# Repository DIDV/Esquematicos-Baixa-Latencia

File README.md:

#Esquematicos Baixa Latência

Repositório dos esquematicos de baixa latência.

Commits baseados nas diferenças nos xmls gerados pelo software [Eagle](http://www.cadsoftusa.com/).

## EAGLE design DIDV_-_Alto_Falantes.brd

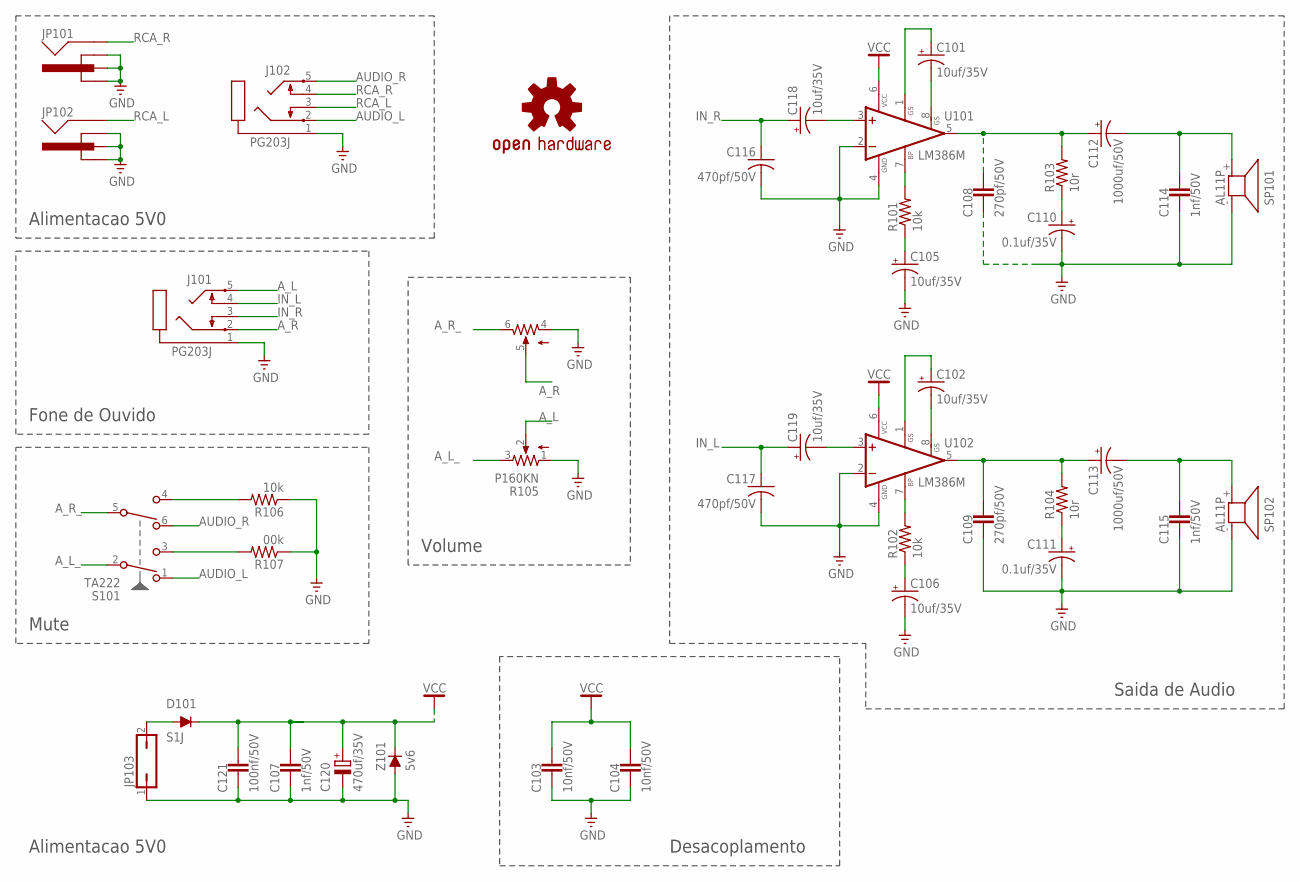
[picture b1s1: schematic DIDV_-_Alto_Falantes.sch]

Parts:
C101, C102, C105, C106, C118, C119: 10uf/35V; E2-5
C103, C104: 10nf/50V; C0805
C107, C114, C115: 1nf/50V; C0805
C108, C109: 270pf/50V; C0805
C110, C111: 0.1uf/35V; E2-5
C112, C113: 1000uf/50V; E3,5-10
C116, C117: 470pf/50V; C0603
C120: 470uf/35V; E3,5-10
C121: 100nf/50V; C0805
D101: S1J; DO214AC
J101, J102: PG203J
JP101, JP102: RCA
JP103: JP1Q; JP1
LOGO101: OSHW-LOGOL; OSHW-LOGO-L
R101, R102, R106: 10k; R1206
R103, R104: 10r; R1206
R105: P160KN
R107: 00k; R1206
S101: TA222
SP101, SP102: AL11P
U101, U102: LM386M; SO08
Z101: 5v6; SOT23

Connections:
AUDIO_L: J102.2, S101.1 (A-NC)
AUDIO_R: J102.5, S101.6 (B-NC)
A_L: J101.5, R105.2
A_L_: R105.3, S101.2 (A-COM)
A_R: J101.2, R105.5 (6)
A_R_: R105.6 (5), S101.5 (B-COM)
GND: C103.2, C104.2, C105.-, C106.-, C107.2, C108.2, C109.2, C110.-, C111.-, C114.2, C115.2, C116.2, C117.2, C120.-, C121.2, J101.1, J102.1, JP101._1GND (GND1), JP101._2GND (GND2), JP101._GND (GND), JP102._1GND (GND1), JP102._2GND (GND2), JP102._GND (GND), JP103.1, R105.1, R105.4, R106.1, R107.1, SP101.- (1), SP102.- (1), U101.2 (-IN), U101.4 (GND), U102.2 (-IN), U102.4 (GND), Z101.1 (A)
IN_L: C117.1, C119.+, J101.4
IN_R: C116.1, C118.+, J101.3
unnamed: C105.+, R101.1
unnamed: R101.2, U101.7 (BS2)
unnamed: C110.+, R103.1
unnamed: C108.1, C112.+, R103.2, U101.5 (OUT)
unnamed: C101.-, U101.8 (GAIN)
unnamed: C101.+, U101.1 (GAIN)
unnamed: C118.-, U101.3 (+IN)
unnamed: C113.-, C115.1, SP102.+ (2)
unnamed: C112.-, C114.1, SP101.+ (2)
unnamed: R106.2, S101.4 (B-NO)
unnamed: C106.+, R102.1
unnamed: R102.2, U102.7 (BS2)
unnamed: C111.+, R104.1
unnamed: C109.1, C113.+, R104.2, U102.5 (OUT)
unnamed: C102.-, U102.8 (GAIN)
unnamed: C102.+, U102.1 (GAIN)
unnamed: C119.-, U102.3 (+IN)
unnamed: R107.2, S101.3 (A-NO)
unnamed: D101.A, JP103.2
RCA_L: J102.3, JP102._SIGNAL (SIGNAL)
RCA_R: J102.4, JP101._SIGNAL (SIGNAL)
VCC: C103.1, C104.1, C107.1, C120.+, C121.1, D101.C, U101.6 (VS), U102.6 (VS), Z101.3 (C)

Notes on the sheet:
Alimentacao 5V0
Desacoplamento
Fone de Ouvido
Mute
Volume
Saida de Audio

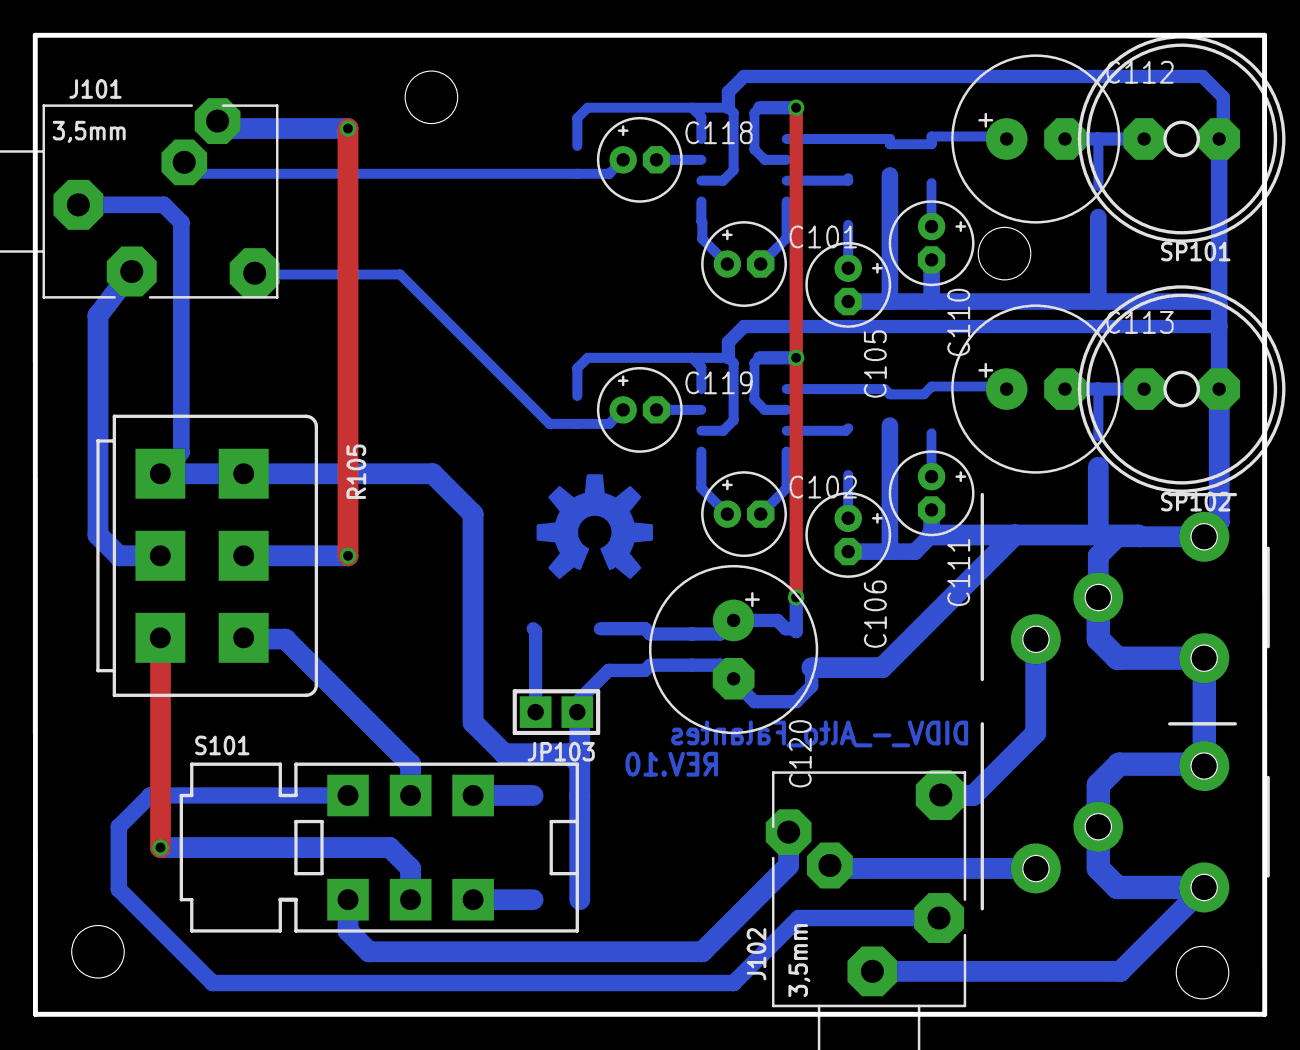
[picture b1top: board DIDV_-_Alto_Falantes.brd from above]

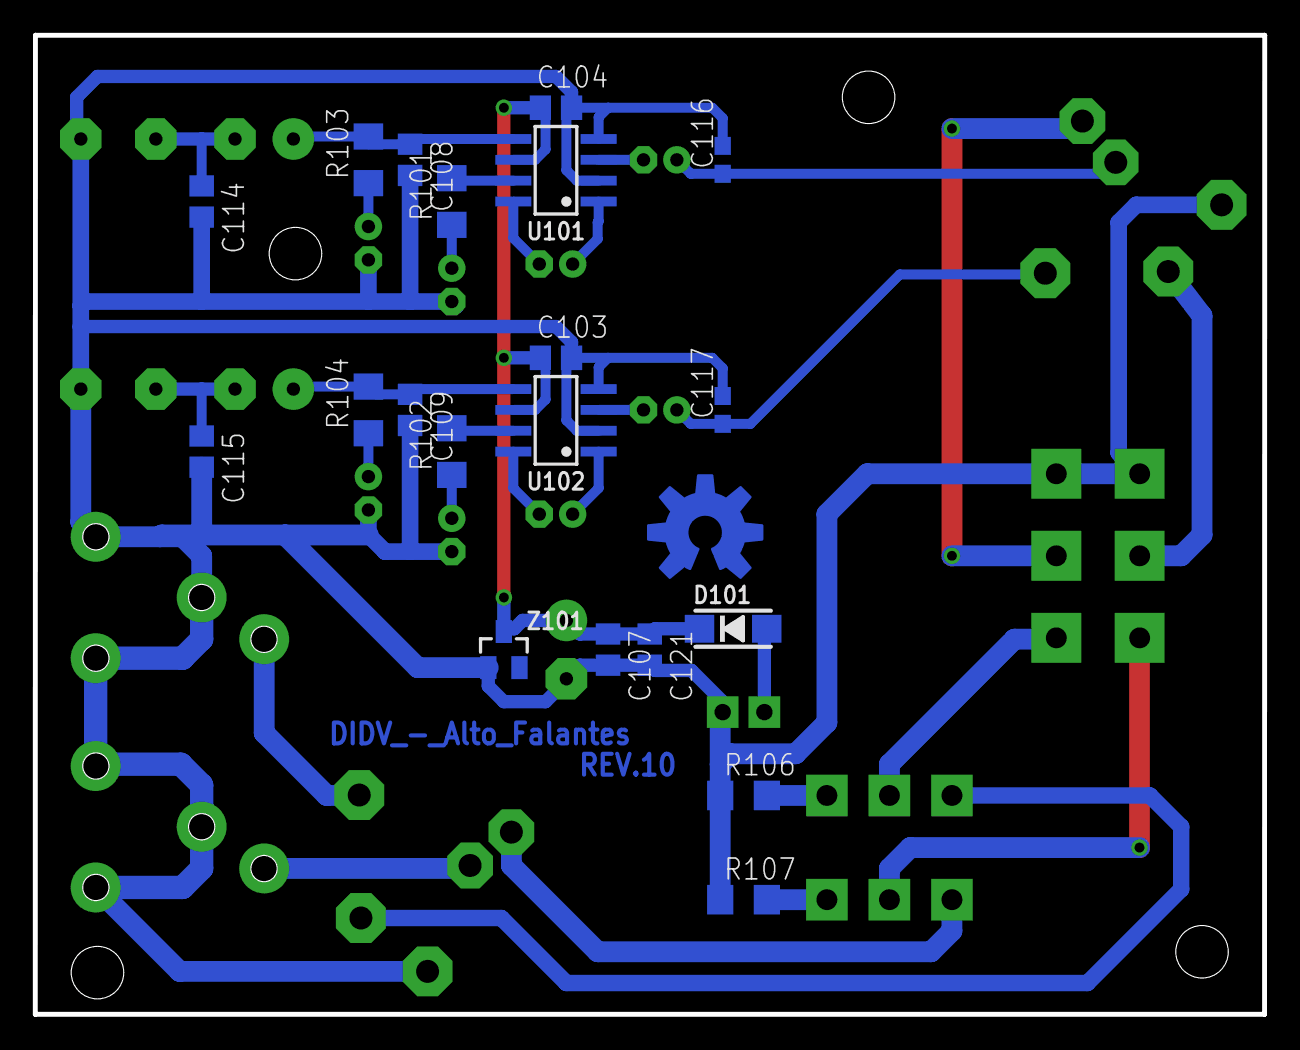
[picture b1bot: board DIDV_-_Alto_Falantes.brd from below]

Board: 2 copper layers, 74.9 x 59.7 mm, 41 parts (20 on the bottom side), 31 nets.

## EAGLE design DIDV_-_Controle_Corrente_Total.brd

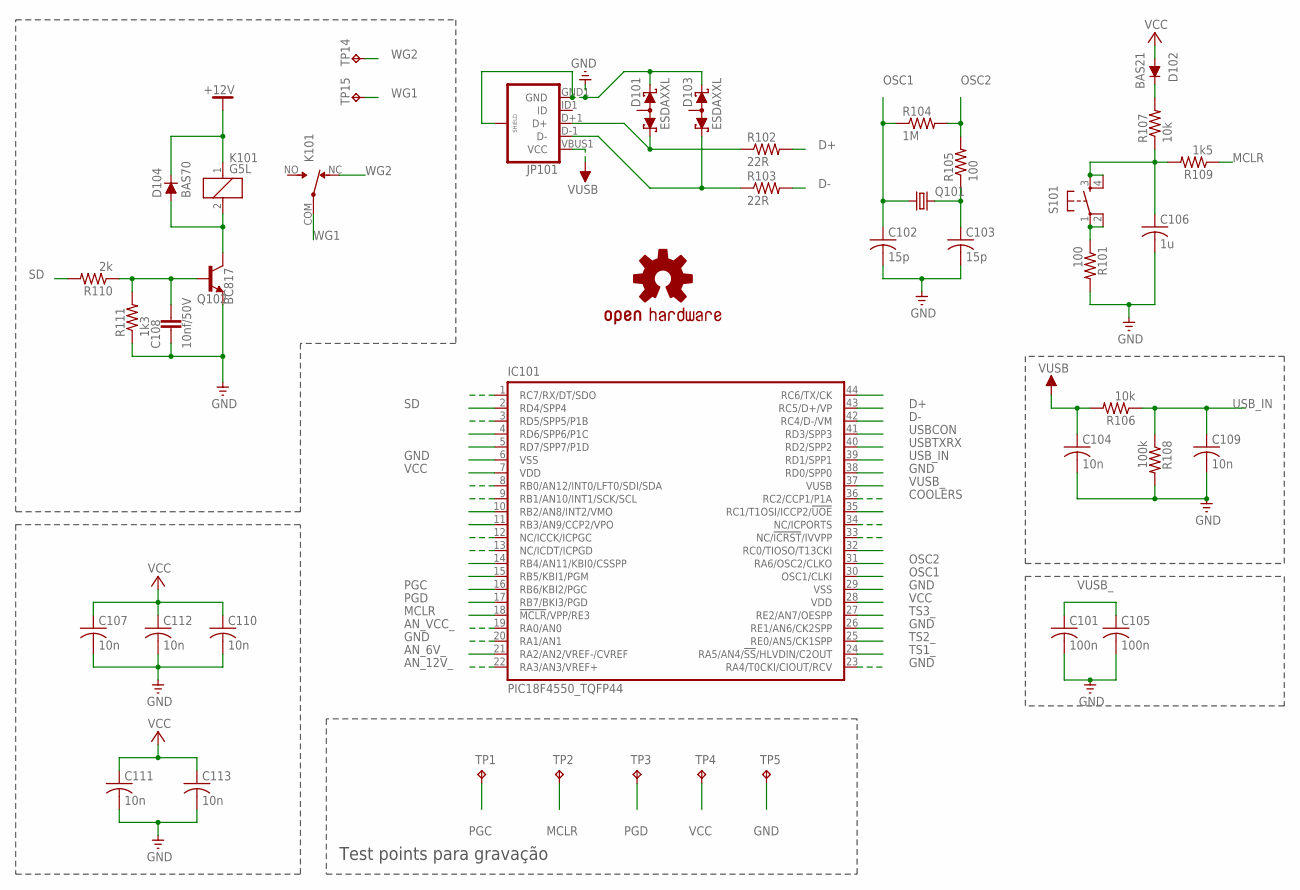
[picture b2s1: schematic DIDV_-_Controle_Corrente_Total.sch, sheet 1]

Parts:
C101, C105: 100n; C0603
C102, C103: 15p; C0603K
C104, C110, C111, C113: 10n; C0805K
C106: 1u; C0805K
C107, C112: 10n; C0603
C108: 10nf/50V; C0603K
C109: 10n; C0603K
D101, D103: ESDAXXL; SOT23
D102: BAS21; SOT23
D104: BAS70; SOT23
IC101: PIC18F4550_TQFP44; TQFP44
JP101: USB_MICROB_PLUGCONN-11752; USB-B-MICRO-SMD_V03
K101: G5L; G5LE
LOGO101: OSHW-LOGOL; OSHW-LOGO-L
Q101: CRYSTALSM49; SM49
Q102: BC817; SOT23-BEC
R101, R105: 100; R0603
R102, R103: 22R; R0603
R104: 1M; R0603
R106, R107: 10k; R0603
R108: 100k; R0603
R109: 1k5; R0603
R110: 2k; R0603
R111: 1k3; R0603
S101: TAC_SWITCHPTH; TACTILE-PTH
TP1, TP2, TP3, TP4, TP5: TPB1,27; B1,27
TP14, TP15: TP-063

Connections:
+12V: D104.3 (C), K101.1; also elsewhere on the board
AN_6V_: IC101.21 (RA2/AN2/VREF-/CVREF); also elsewhere on the board
AN_12V_: IC101.22 (RA3/AN3/VREF+); also elsewhere on the board
AN_VCC_: IC101.19 (RA0/AN0); also elsewhere on the board
COOLERS: IC101.36 (RC2/CCP1/P1A); also elsewhere on the board
D+: IC101.43 (RC5/D+/VP), R102.2
D-: IC101.42 (RC4/D-/VM), R103.2
GND: C101.2, C102.2, C103.2, C104.2, C105.2, C106.2, C107.2, C108.2, C109.2, C110.2, C111.2, C112.2, C113.2, D101.2 (C2), D103.2 (C2), IC101.6 (VSS), IC101.20 (RA1/AN1), IC101.23 (RA4/T0CKI/CIOUT/RCV), IC101.26 (RE1/AN6/CK2SPP), IC101.29 (VSS), IC101.38 (RD0/SPP0), JP101.GND1 (GND), JP101.SHIELD1 (SHIELD), JP101.SHIELD2 (SHIELD), JP101.SHIELD3 (SHIELD), Q102.E, R101.2, R108.2, R111.1, TP5.TP; also elsewhere on the board
MCLR: IC101.18 (!MCLR!/VPP/RE3), R109.1, TP2.TP
unnamed: C103.1, Q101.2, R105.1
unnamed: D102.3 (C), R107.2
unnamed: D104.1 (A), K101.2, Q102.C
unnamed: C108.1, Q102.B, R110.1, R111.2
unnamed: D103.1 (C1), JP101.D-1 (D-), R103.1
unnamed: D101.1 (C1), JP101.D+1 (D+), R102.1
unnamed: R101.1, S101.1, S101.2
OSC1: C102.1, IC101.30 (OSC1/CLKI), Q101.1, R104.1
OSC2: IC101.31 (RA6/OSC2/CLKO), R104.2, R105.2
PGC: IC101.16 (RB6/KBI2/PGC), TP1.TP
PGD: IC101.17 (RB7/BKI3/PGD), TP3.TP
SD: IC101.2 (RD4/SPP4), R110.2
TS1_: IC101.24 (RA5/AN4/!SS!/HLVDIN/C2OUT); also elsewhere on the board
TS2_: IC101.25 (RE0/AN5/CK1SPP); also elsewhere on the board
TS3_: IC101.27 (RE2/AN7/OESPP); also elsewhere on the board
USBCON: IC101.41 (RD3/SPP3); also elsewhere on the board
USBTXRX: IC101.40 (RD2/SPP2); also elsewhere on the board
USB_IN: C109.1, IC101.39 (RD1/SPP1), R106.1, R108.1
U_MCLR: C106.1, R107.1, R109.2, S101.3, S101.4
VCC: C107.1, C110.1, C111.1, C112.1, C113.1, D102.1 (A), IC101.7 (VDD), IC101.28 (VDD), TP4.TP; also elsewhere on the board
VUSB: C104.1, JP101.VBUS1 (VCC), R106.2
VUSB_: C101.1, C105.1, IC101.37 (VUSB)
WG1: K101.COM, TP15.1
WG2: K101.NC, TP14.1

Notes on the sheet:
Test points para gravação

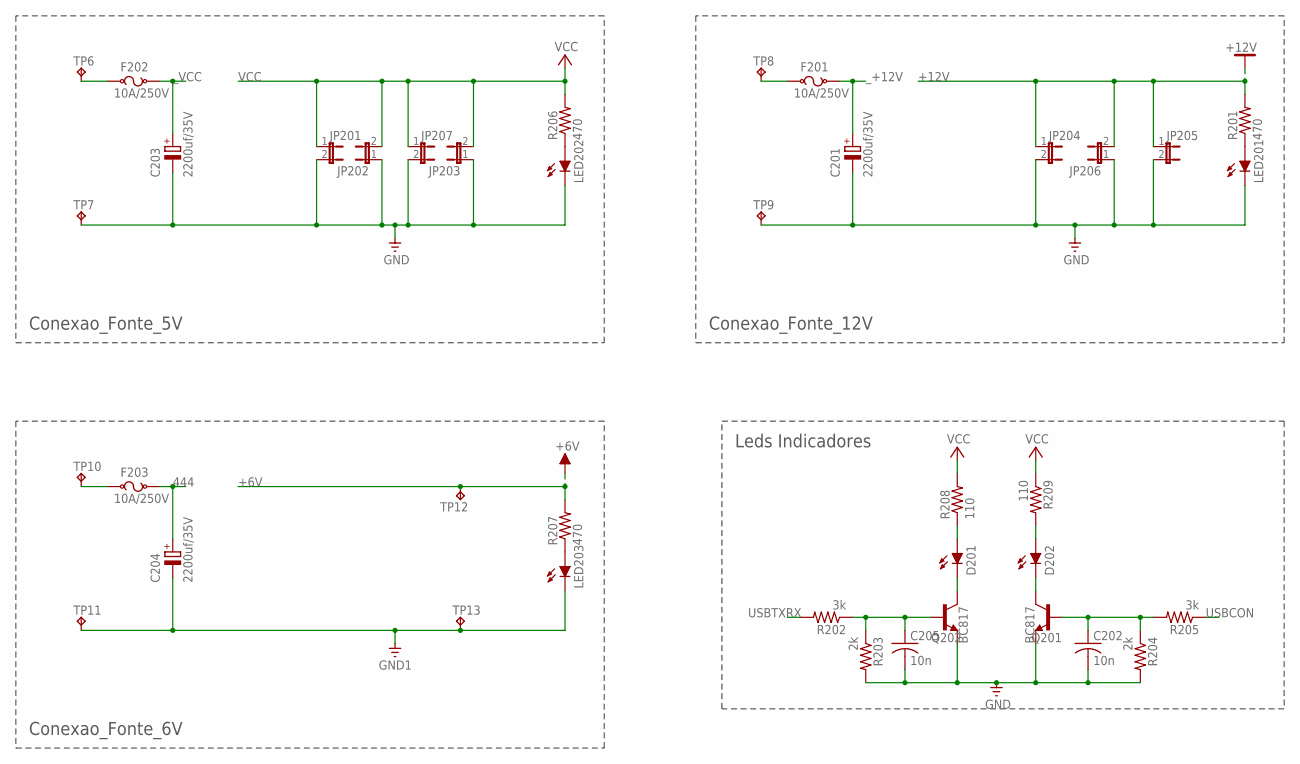
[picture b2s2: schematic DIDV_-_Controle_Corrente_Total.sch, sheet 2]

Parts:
C201, C203, C204: 2200uf/35V; E3,5-10
C202, C205: 10n; C0603
D201, D202: LEDTOPLED-SANTANA; MINI-TOPLED-SANTANA
F201, F202, F203: 10A/250V; KS9V
JP201, JP202, JP203, JP204, JP205, JP206, JP207: JP1EY; JP1Y
LED201, LED202, LED203: LEDP-LCC-2; P-LCC-2
Q201, Q202: BC817; SOT23-BEC
R201, R206, R207: 470; R1206
R202, R205: 3k; R0603
R203, R204: 2k; R0603
R208, R209: 110; R1206
TP6, TP7, TP8, TP9, TP10, TP11, TP12, TP13: TP-063

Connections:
444: C204.+, F203.2; also elsewhere on the board
+6V: R207.2, TP12.1; also elsewhere on the board
+12V: JP204.1, JP205.1, JP206.2, R201.2; also elsewhere on the board
GND: C201.-, C202.2, C203.-, C205.2, JP201.2, JP202.1, JP203.1, JP204.2, JP205.2, JP206.1, JP207.2, LED201.C, LED202.C, Q201.E, Q202.E, R203.2, R204.2, TP7.1, TP9.1; also elsewhere on the board
GND1: C204.-, LED203.C, TP11.1, TP13.1
unnamed: LED202.A, R206.1
unnamed: LED201.A, R201.1
unnamed: F201.1, TP8.1
unnamed: LED203.A, R207.1
unnamed: F203.1, TP10.1
unnamed: D201.A, R208.1
unnamed: D202.A, R209.2
unnamed: C205.1, Q202.B, R202.1, R203.1
unnamed: C202.1, Q201.B, R204.1, R205.2
unnamed: D201.C, Q202.C
unnamed: D202.C, Q201.C
unnamed: F202.1, TP6.1
USBCON: R205.1; also elsewhere on the board
USBTXRX: R202.2; also elsewhere on the board
VCC: JP201.1, JP202.2, JP203.2, JP207.1, R206.2, R208.2, R209.1; also elsewhere on the board
_+12V: C201.+, F201.2; also elsewhere on the board
_VCC: C203.+, F202.2; also elsewhere on the board

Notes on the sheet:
Conexao_Fonte_5V
Conexao_Fonte_12V
Conexao_Fonte_6V
Leds Indicadores

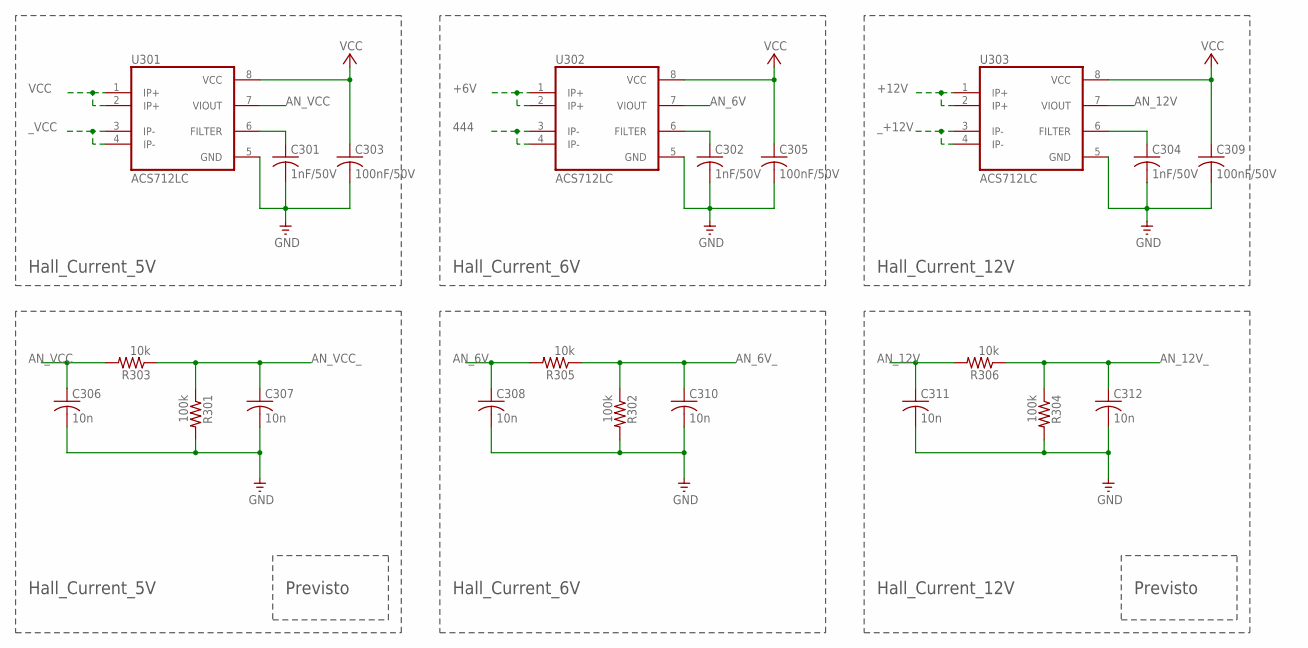
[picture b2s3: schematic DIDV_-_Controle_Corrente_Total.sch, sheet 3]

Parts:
C301, C302, C304: 1nF/50V; C0603
C303, C305, C309: 100nF/50V; C0805
C306, C308, C311: 10n; C0805K
C307, C310, C312: 10n; C0603K
R301, R302, R304: 100k; R0603
R303, R305, R306: 10k; R0603
U301, U302, U303: ACS712LC; SO08

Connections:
444: U302.3 (IP-), U302.4 (IP-); also elsewhere on the board
+6V: U302.1 (IP+), U302.2 (IP+); also elsewhere on the board
+12V: U303.1 (IP+), U303.2 (IP+); also elsewhere on the board
AN_6V: C308.1, R305.2, U302.7 (VIOUT)
AN_6V_: C310.1, R302.1, R305.1; also elsewhere on the board
AN_12V: C311.1, R306.2, U303.7 (VIOUT)
AN_12V_: C312.1, R304.1, R306.1; also elsewhere on the board
AN_VCC: C306.1, R303.2, U301.7 (VIOUT)
AN_VCC_: C307.1, R301.1, R303.1; also elsewhere on the board
GND: C301.2, C302.2, C303.2, C304.2, C305.2, C306.2, C307.2, C308.2, C309.2, C310.2, C311.2, C312.2, R301.2, R302.2, R304.2, U301.5 (GND), U302.5 (GND), U303.5 (GND); also elsewhere on the board
unnamed: C302.1, U302.6 (FILTER)
unnamed: C304.1, U303.6 (FILTER)
unnamed: C301.1, U301.6 (FILTER)
VCC: C303.1, C305.1, C309.1, U301.1 (IP+), U301.2 (IP+), U301.8 (VCC), U302.8 (VCC), U303.8 (VCC); also elsewhere on the board
_+12V: U303.3 (IP-), U303.4 (IP-); also elsewhere on the board
_VCC: U301.3 (IP-), U301.4 (IP-); also elsewhere on the board

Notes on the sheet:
Hall_Current_5V
Hall_Current_6V
Hall_Current_12V
Previsto

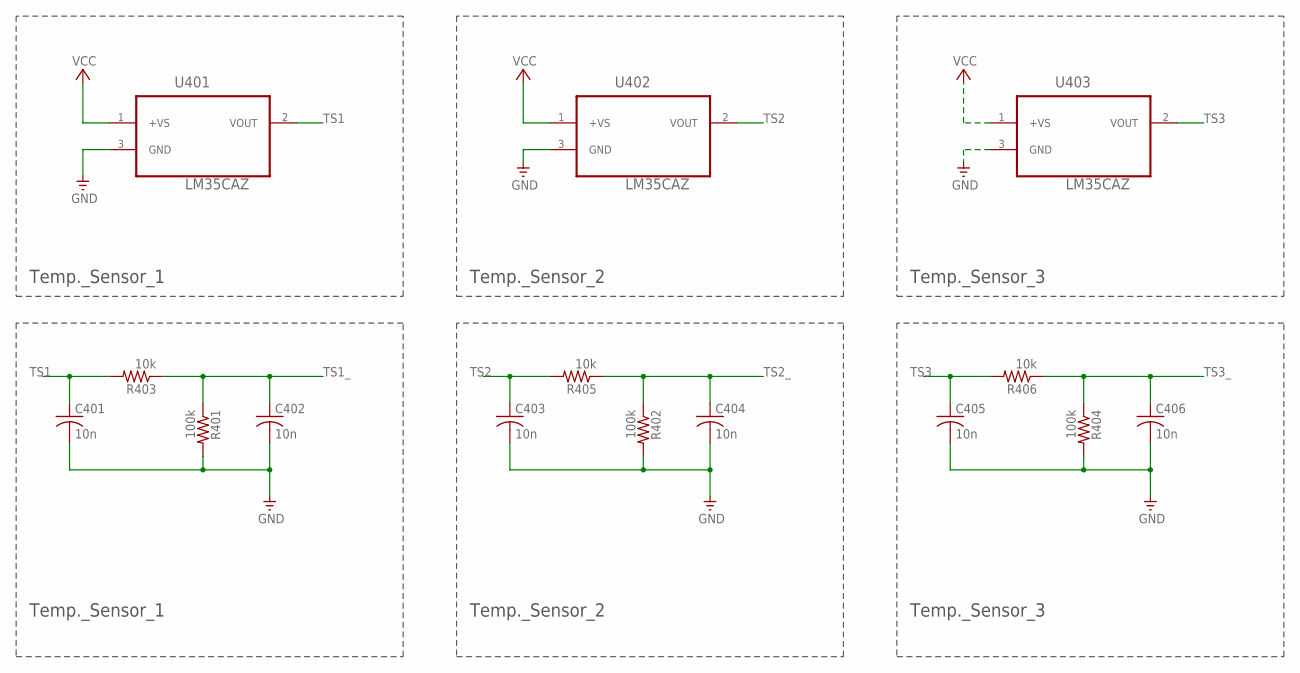
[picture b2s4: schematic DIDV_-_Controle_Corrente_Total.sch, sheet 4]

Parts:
C401, C403, C405: 10n; C0805K
C402, C404, C406: 10n; C0603K
R401, R402, R404: 100k; R0603
R403, R405, R406: 10k; R0603
U401, U402, U403: LM35CAZ; TO127P254X495-3P

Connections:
GND: C401.2, C402.2, C403.2, C404.2, C405.2, C406.2, R401.2, R402.2, R404.2, U401.3 (GND), U402.3 (GND), U403.3 (GND); also elsewhere on the board
TS1: C401.1, R403.2, U401.2 (VOUT)
TS1_: C402.1, R401.1, R403.1; also elsewhere on the board
TS2: C403.1, R405.2, U402.2 (VOUT)
TS2_: C404.1, R402.1, R405.1; also elsewhere on the board
TS3: C405.1, R406.2, U403.2 (VOUT)
TS3_: C406.1, R404.1, R406.1; also elsewhere on the board
VCC: U401.1 (+VS), U402.1 (+VS), U403.1 (+VS); also elsewhere on the board

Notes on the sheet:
Temp._Sensor_1
Temp._Sensor_2
Temp._Sensor_3

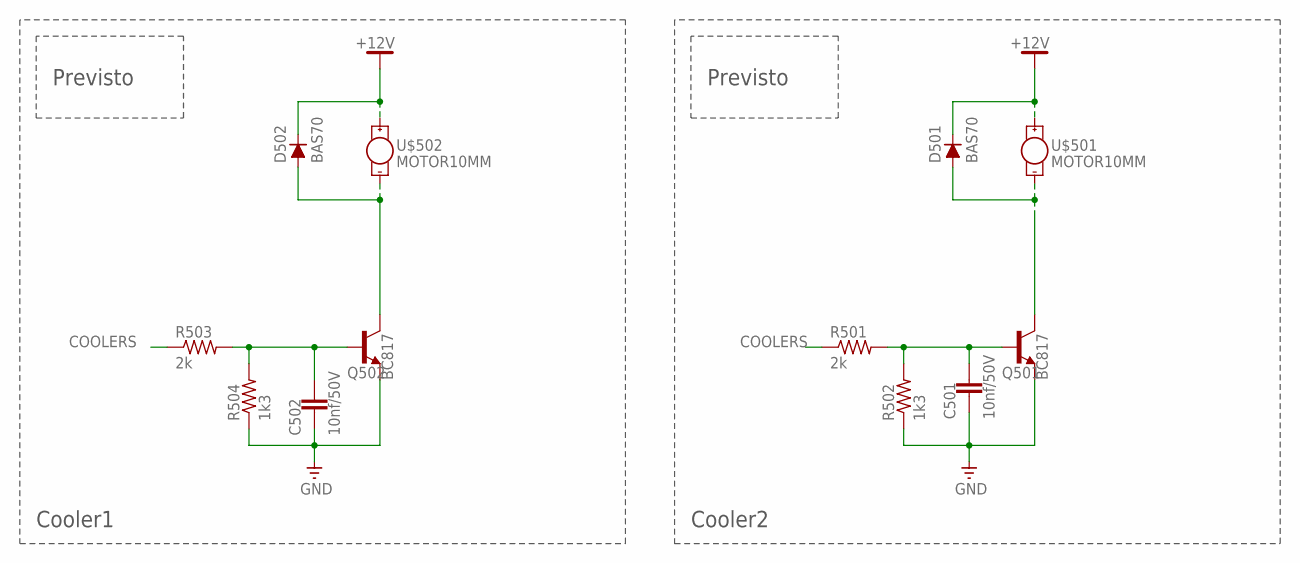
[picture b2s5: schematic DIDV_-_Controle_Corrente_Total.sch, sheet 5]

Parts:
C501, C502: 10nf/50V; C0603K
D501, D502: BAS70; SOT23
Q501, Q502: BC817; SOT23-BEC
R501, R503: 2k; R0603
R502, R504: 1k3; R0603
U$501, U$502: MOTOR10MM; VIBE-MOTOR-10MM

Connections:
+12V: D501.3 (C), D502.3 (C), U$501.+, U$502.+; also elsewhere on the board
COOLERS: R501.1, R503.1; also elsewhere on the board
GND: C501.2, C502.2, Q501.E, Q502.E, R502.1, R504.1; also elsewhere on the board
unnamed: C501.1, Q501.B, R501.2, R502.2
unnamed: D501.1 (A), Q501.C, U$501.-
unnamed: C502.1, Q502.B, R503.2, R504.2
unnamed: D502.1 (A), Q502.C, U$502.-

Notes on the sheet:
Cooler1
Previsto
Cooler2

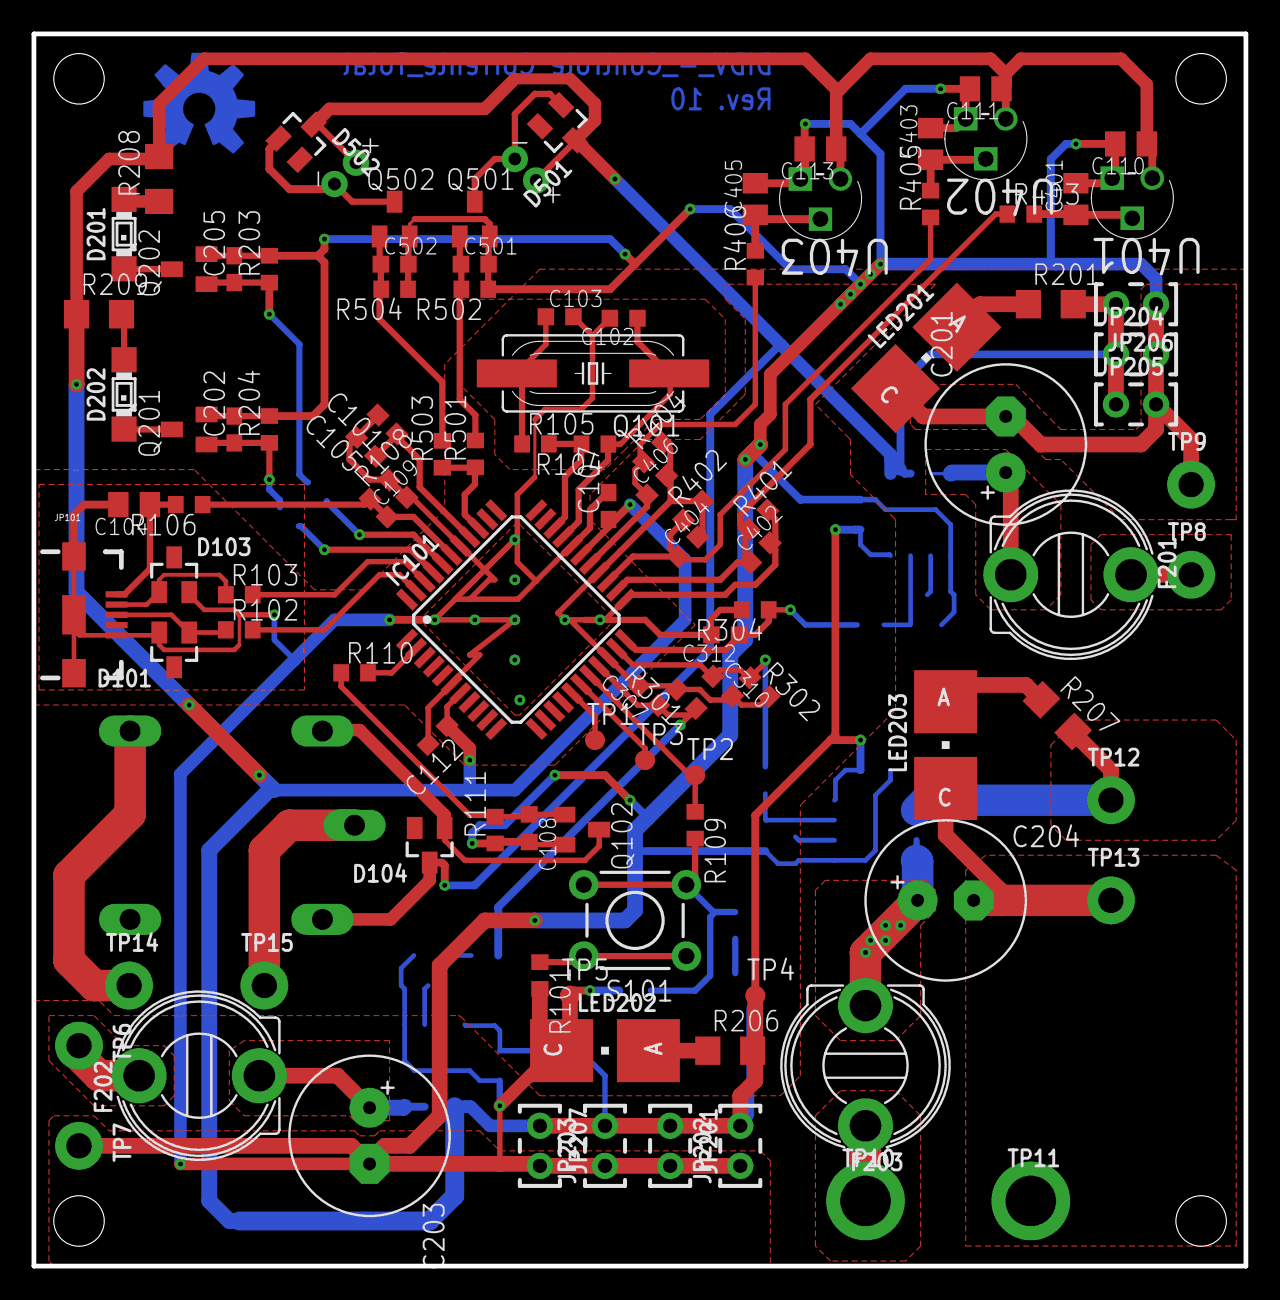
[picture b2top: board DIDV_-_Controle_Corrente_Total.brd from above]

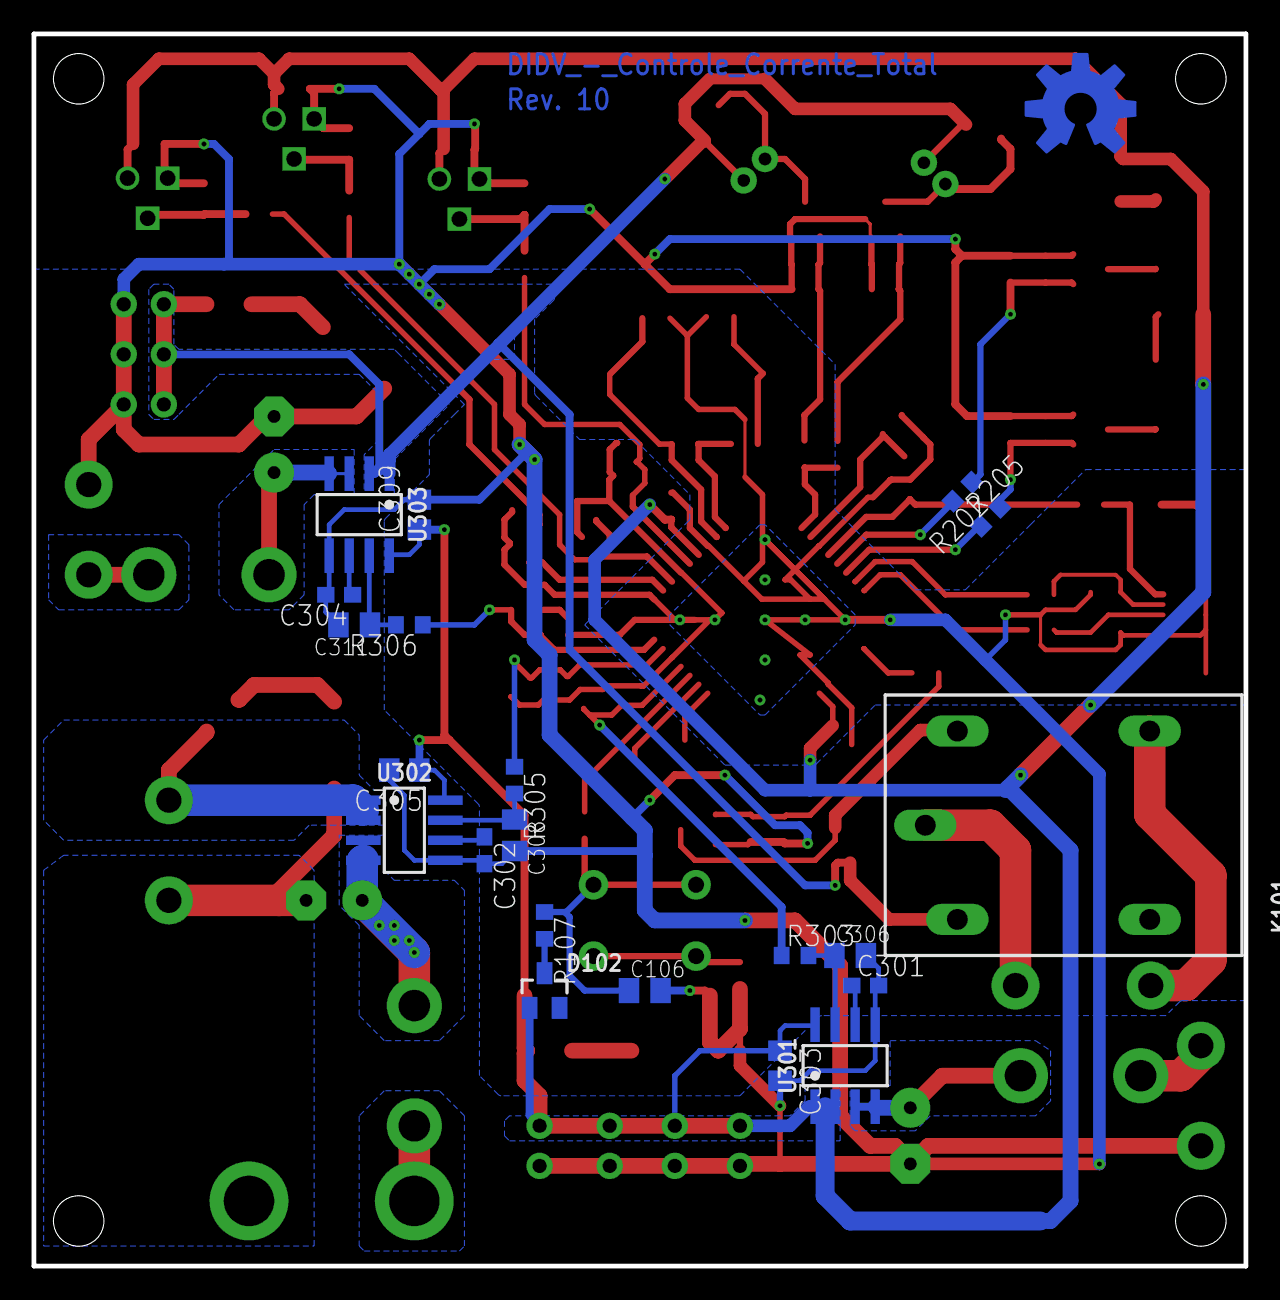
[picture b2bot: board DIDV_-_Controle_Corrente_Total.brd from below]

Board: 2 copper layers, 76.8 x 78.1 mm, 129 parts (21 on the bottom side), 63 nets.

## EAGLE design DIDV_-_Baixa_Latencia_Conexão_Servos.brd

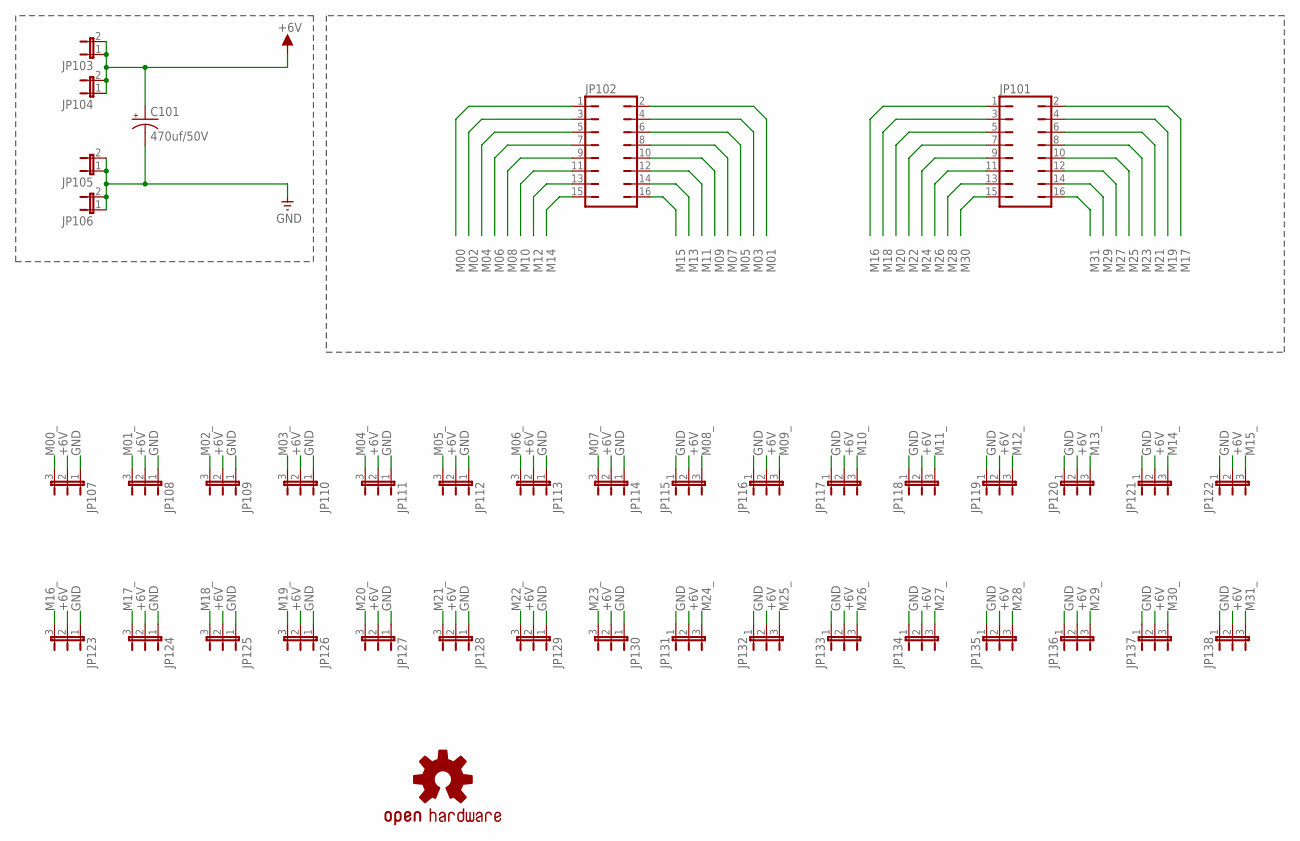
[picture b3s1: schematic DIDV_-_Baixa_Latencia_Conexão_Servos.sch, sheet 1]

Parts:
C101: 470uf/50V; 140CLH-1010
JP101, JP102: JP8Q
JP103, JP104, JP105, JP106: JP1E; JP1
JP107, JP108, JP109, JP110, JP111, JP112, JP113, JP114, JP115, JP116, JP117, JP118, JP119, JP120, JP121, JP122, JP123, JP124, JP125, JP126, JP127, JP128, JP129, JP130, JP131, JP132, JP133, JP134, JP135, JP136, JP137, JP138: JP2E; JP2
LOGO101: OSHW-LOGOL; OSHW-LOGO-L

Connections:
+6V: C101.+, JP103.1, JP103.2, JP104.1, JP104.2, JP107.2, JP108.2, JP109.2, JP110.2, JP111.2, JP112.2, JP113.2, JP114.2, JP115.2, JP116.2, JP117.2, JP118.2, JP119.2, JP120.2, JP121.2, JP122.2, JP123.2, JP124.2, JP125.2, JP126.2, JP127.2, JP128.2, JP129.2, JP130.2, JP131.2, JP132.2, JP133.2, JP134.2, JP135.2, JP136.2, JP137.2, JP138.2
GND: C101.-, JP105.1, JP105.2, JP106.1, JP106.2, JP107.1, JP108.1, JP109.1, JP110.1, JP111.1, JP112.1, JP113.1, JP114.1, JP115.1, JP116.1, JP117.1, JP118.1, JP119.1, JP120.1, JP121.1, JP122.1, JP123.1, JP124.1, JP125.1, JP126.1, JP127.1, JP128.1, JP129.1, JP130.1, JP131.1, JP132.1, JP133.1, JP134.1, JP135.1, JP136.1, JP137.1, JP138.1; also elsewhere on the board
M00: JP102.1; also elsewhere on the board
M00_: JP107.3; also elsewhere on the board
M01: JP102.2; also elsewhere on the board
M01_: JP108.3; also elsewhere on the board
M02: JP102.3; also elsewhere on the board
M02_: JP109.3; also elsewhere on the board
M03: JP102.4; also elsewhere on the board
M03_: JP110.3; also elsewhere on the board
M04: JP102.5; also elsewhere on the board
M04_: JP111.3; also elsewhere on the board
M05: JP102.6; also elsewhere on the board
M05_: JP112.3; also elsewhere on the board
M06: JP102.7; also elsewhere on the board
M06_: JP113.3; also elsewhere on the board
M07: JP102.8; also elsewhere on the board
M07_: JP114.3; also elsewhere on the board
M08: JP102.9; also elsewhere on the board
M08_: JP115.3; also elsewhere on the board
M09: JP102.10; also elsewhere on the board
M09_: JP116.3; also elsewhere on the board
M10: JP102.11; also elsewhere on the board
M10_: JP117.3; also elsewhere on the board
M11: JP102.12; also elsewhere on the board
M11_: JP118.3; also elsewhere on the board
M12: JP102.13; also elsewhere on the board
M12_: JP119.3; also elsewhere on the board
M13: JP102.14; also elsewhere on the board
M13_: JP120.3; also elsewhere on the board
M14: JP102.15; also elsewhere on the board
M14_: JP121.3; also elsewhere on the board
M15: JP102.16; also elsewhere on the board
M15_: JP122.3; also elsewhere on the board
M16: JP101.1; also elsewhere on the board
M16_: JP123.3; also elsewhere on the board
M17: JP101.2; also elsewhere on the board
M17_: JP124.3; also elsewhere on the board
M18: JP101.3; also elsewhere on the board
M18_: JP125.3; also elsewhere on the board
M19: JP101.4; also elsewhere on the board
M19_: JP126.3; also elsewhere on the board
M20: JP101.5; also elsewhere on the board
M20_: JP127.3; also elsewhere on the board
M21: JP101.6; also elsewhere on the board
M21_: JP128.3; also elsewhere on the board
M22: JP101.7; also elsewhere on the board
M22_: JP129.3; also elsewhere on the board
M23: JP101.8; also elsewhere on the board
M23_: JP130.3; also elsewhere on the board
M24: JP101.9; also elsewhere on the board
M24_: JP131.3; also elsewhere on the board
M25: JP101.10; also elsewhere on the board
M25_: JP132.3; also elsewhere on the board
M26: JP101.11; also elsewhere on the board
M26_: JP133.3; also elsewhere on the board
M27: JP101.12; also elsewhere on the board
M27_: JP134.3; also elsewhere on the board
M28: JP101.13; also elsewhere on the board
M28_: JP135.3; also elsewhere on the board
M29: JP101.14; also elsewhere on the board
M29_: JP136.3; also elsewhere on the board
M30: JP101.15; also elsewhere on the board
M30_: JP137.3; also elsewhere on the board
M31: JP101.16; also elsewhere on the board
M31_: JP138.3; also elsewhere on the board

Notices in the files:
parts and their libraries:
OpenHW_BOT: Licensing: Creative Commons ShareAlike 4.0 International - https://creativecommons.org/licenses/by-sa/4.0
supply0: Copyright (C) 2007, Bob Starr
switch-e-switch: Copyright (C) 2010, Bob Starr
allegro-micro: Copyright (C) 2008, Bob Starr
